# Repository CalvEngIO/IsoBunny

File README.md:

# IsoBunny
Optoisolator breakout module

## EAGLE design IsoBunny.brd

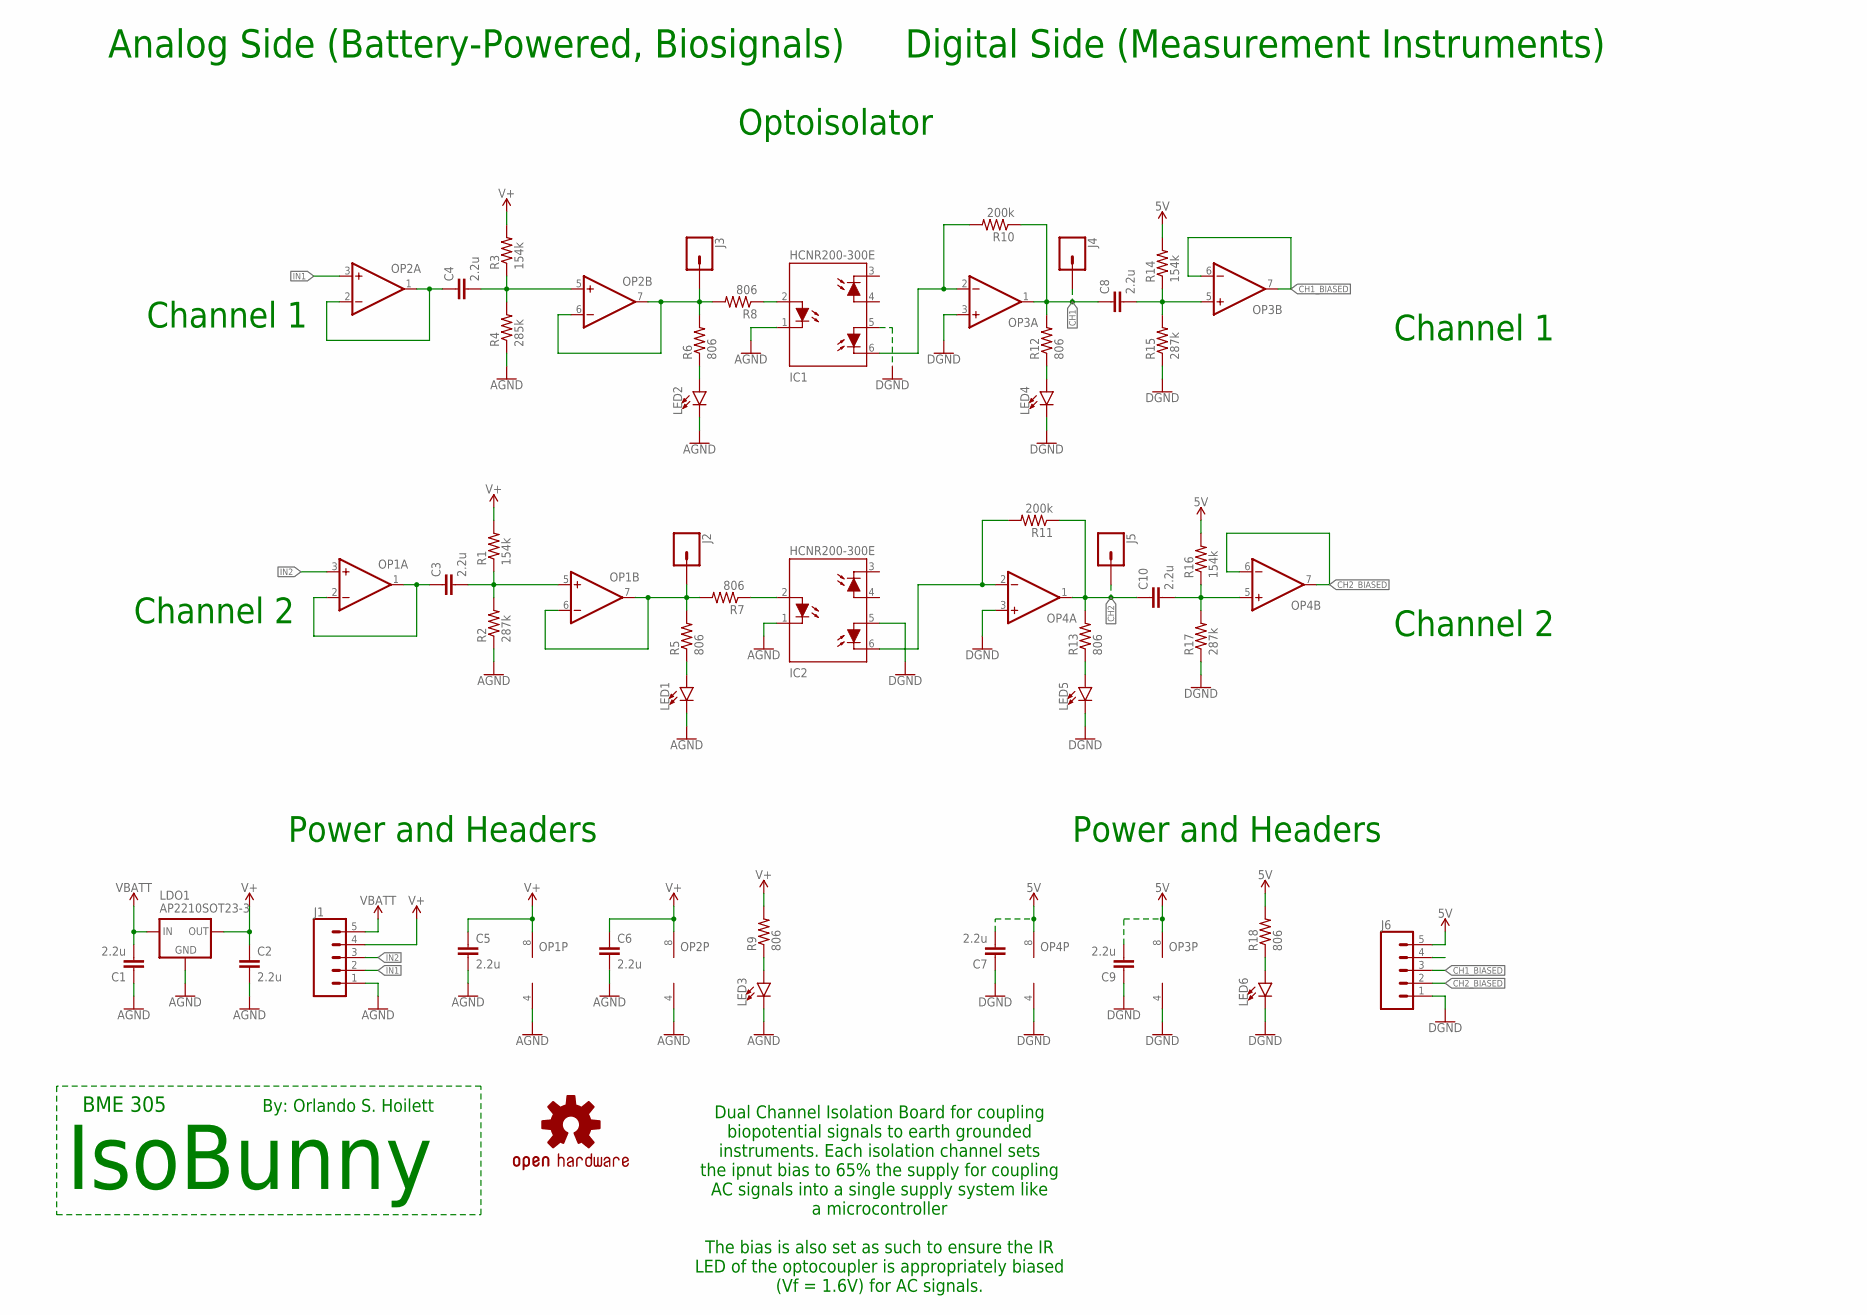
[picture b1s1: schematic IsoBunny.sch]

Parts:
C1, C2, C3, C4, C5, C6, C7, C8, C9, C10: 2.2u; C0603
IC1, IC2: HCNR200-300E; DIP8-400
J1, J6: CONN_05; 1X05
J2, J3, J4, J5: CONN_01PTH_NO_SILK_KIT; 1X01NS_KIT
LDO1: AP2210SOT23-3; SOT23
LED1, LED2, LED3, LED4, LED5, LED6: LED5MM; LED_5MM
LOGO1: OSHW-LOGOL; OSHW-LOGO-L
OP1, OP2, OP3, OP4: OP-DUALR; SO8
R1, R3, R14, R16: 154k; R0603
R2, R15, R17: 287k; R0603
R4: 285k; R0603
R5, R6, R7, R8, R9, R12, R13, R18: 806; R0603
R10, R11: 200k; R0603
REV1: REVISION.A; REV.A
U$1: PURDUE_BME_HANDLE; PURDUE_BME_HANDLE.1

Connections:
5V: C7.2, C9.2, J6.5, OP3.8 (V+), OP4.8 (V+), R14.2, R16.2, R18.2
AGND: C1.1, C2.2, C5.2, C6.2, IC1.1 (C), IC2.1 (C), J1.1, LDO1.1 (GND), LED1.K (C), LED2.K (C), LED3.K (C), OP1.4 (V-), OP2.4 (V-), R2.1, R4.1
CH1: C8.1, J4.1, OP3.1 (OUT), R10.1, R12.2
CH1_BIASED: J6.3, OP3.6 (-IN), OP3.7 (OUT)
CH2: C10.1, J5.1, OP4.1 (OUT), R11.1, R13.2
CH2_BIASED: J6.2, OP4.6 (-IN), OP4.7 (OUT)
DGND: C7.1, C9.1, IC1.5 (A2), IC2.5 (A2), J6.1, LED4.K (C), LED5.K (C), LED6.K (C), OP3.3 (+IN), OP3.4 (V-), OP4.3 (+IN), OP4.4 (V-), R15.1, R17.1
IN1: J1.2, OP2.3 (+IN)
IN2: J1.3, OP1.3 (+IN)
unnamed: C4.1, OP2.1 (OUT), OP2.2 (-IN)
unnamed: LED3.A, R9.1
unnamed: C4.2, OP2.5 (+IN), R3.1, R4.2
unnamed: C3.1, OP1.1 (OUT), OP1.2 (-IN)
unnamed: IC1.6 (C2), OP3.2 (-IN), R10.2
unnamed: C3.2, OP1.5 (+IN), R1.1, R2.2
unnamed: IC2.6 (C2), OP4.2 (-IN), R11.2
unnamed: LED6.A, R18.1
unnamed: IC2.2 (A), R7.1
unnamed: C10.2, OP4.5 (+IN), R16.1, R17.2
unnamed: LED2.A, R6.1
unnamed: IC1.2 (A), R8.1
unnamed: C8.2, OP3.5 (+IN), R14.1, R15.2
unnamed: LED4.A, R12.1
unnamed: LED1.A, R5.1
unnamed: LED5.A, R13.1
OUT1: J3.1, OP2.6 (-IN), OP2.7 (OUT), R6.2, R8.2
OUT2: J2.1, OP1.6 (-IN), OP1.7 (OUT), R5.2, R7.2
V+: C2.1, C5.1, C6.1, J1.4, LDO1.2 (OUT), OP1.8 (V+), OP2.8 (V+), R1.2, R3.2, R9.2
V_BATT: C1.2, J1.5, LDO1.3 (IN)

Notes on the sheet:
Analog Side (Battery-Powered, Biosignals)
Digital Side (Measurement Instruments)
Channel 1
Channel 2
Power and Headers
Optoisolator
Dual Channel Isolation Board for coupling biopotential signals to earth grounded instruments. Each isolation channel sets the ipnut bias to 65% the supply for coupling AC signals into a single supply system like a microcontroller The bias is also set as such to ensure the IR LED of the optocoupler 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
IsoBunny
BME 305
By: Orlando S. Hoilett

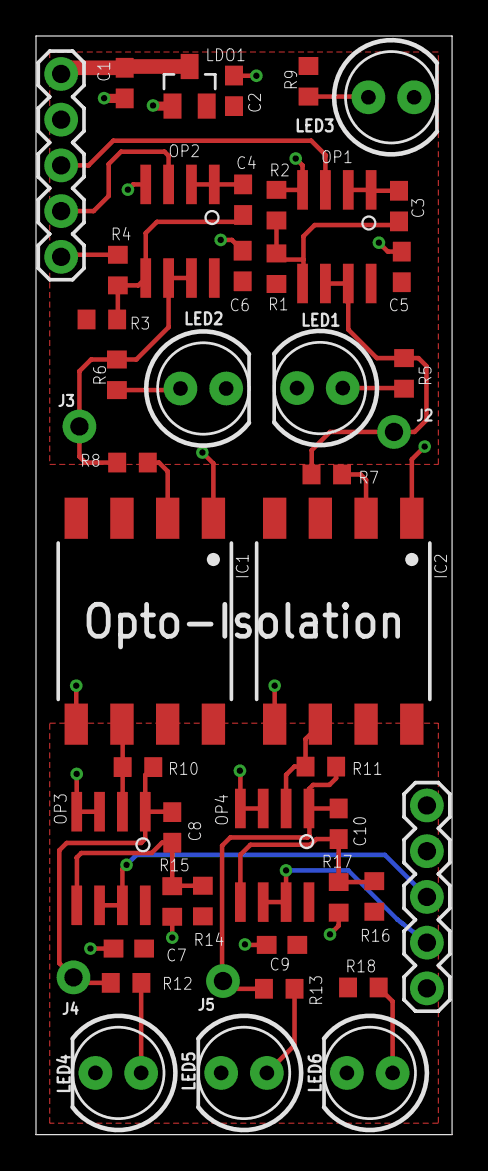
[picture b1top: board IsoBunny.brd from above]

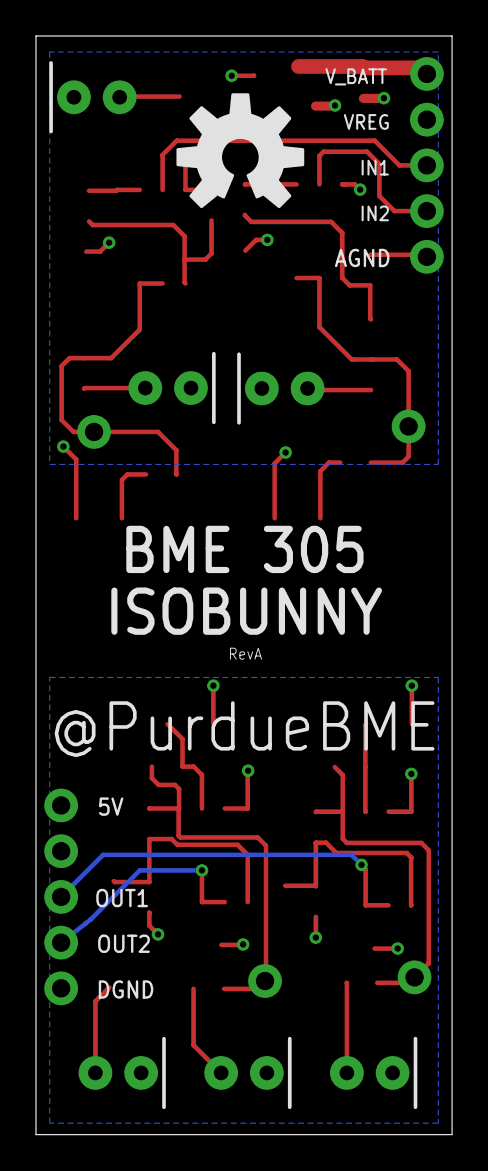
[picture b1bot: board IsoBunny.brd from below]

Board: 2 copper layers, 23.1 x 61.0 mm, 50 parts (3 on the bottom side), 29 nets.

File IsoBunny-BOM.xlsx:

IsoBunny Rev B |  |  |  |  |  |  |  |  |  |  | Total | 13.659999999999998 |  | 0.41860000000000003
BOM # | Comment | Designator | Description | Mounting Type | Package | Manufacturer | Manufacturer Part Number | Supplier | Supplier Part Number | Price per unit | Quantity | Price Total | 100 units | Price Total
1 | MCP6002 | OP1,OP4 | General Purpose Amplifier 2 Circuit Rail-to-Rail 8-SOIC | SMD | 8-SOIC | Microchip Technology | MCP6002T-I/SN | Digi-Key | MCP6002T-I/SNCT-ND | 0.34 | 2 | 0.68 |  | 0
2 | LM2904 | OP2,OP3 | General Purpose Amplifier 2 Circuit 8-SO | SMD | 8-SOIC | Diodes Incorporated | LM2904QS-13 | Digi-Key | LM2904QS-13DICT-ND | 0.38 | 2 | 0.76 | 0.20930000000000001 | 0.41860000000000003
3 | AP2210N-5.0 | LDO1 | Linear Voltage Regulator IC 1 Output 300mA SOT-23-5 | SMD | SOT-23-5 | Diodes Incorporated | AP2210N-5.0TRG1 | Digi-Key | AP2210N-5.0TRG1DICT-ND | 0.43 | 1 | 0.43 |  | 0
4 | HCNR200-300E | IC1,IC2 | Optoisolator Photovoltaic, Linearized Output 5000Vrms 1 Channel 8-DIP Gull Wing | SMD | 8-SMD, Gull Wing | Broadcom Limited | HCNR200-300E | Digi-Key | 516-1608-5-ND | 4.09 | 2 | 8.18 |  | 0
5 | Header Pins | J1,J2,J3,J4,J5,J6 | Connector Header Through Hole 40 position 0.100" (2.54mm)' | THT |  | Sullins Connector Solutions | PREC040SAAN-RC | Digi-Key | S1012EC-40-ND | 0.51 | 1 | 0.51 |  | 0
6 | 2.2uF capacitor | C1, C2,C3,C4,C5,C6,C7,C8,C9,C10 | 16V, X5R | SMD | 0603 | Murata Electronics North America | GRM188R61C225KE15D | Digi-Key | 490-3296-1-ND | 0.13 | 10 | 1.3 |  | 0
7 | 806 Ohm resistor | R5,R6,R7,R8,R9,R12,R13,R18 | 806 Ohms ±1% 0.1W, 1/10W Chip Resistor 0603 (1608 Metric) Automotive AEC-Q200 T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 | SMD | 0603 | Stackpole Electronics Inc. | RMCF0603FT806R | Digi-Key | RMCF0603FT806RCT-ND | 0.1 | 6 | 0.60000000000000009 |  | 0
8 | 154k resistor | R1,R3,R14,R16 | 154 kOhms ±1% 0.1W, 1/10W Chip Resistor 0603 (1608 Metric) Automotive AEC-Q200 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 | SMD | 0603 | Stackpole Electronics Inc. | RMCF0603FT154K | Digi-Key | RMCF0603FT154KCT-ND | 0.1 | 4 | 0.4 |  | 0
9 | 200k resistor | R10,R11 | 200 kOhms ±1% 0.1W, 1/10W Chip Resistor 0603 (1608 Metric) Moisture Resistant T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 | SMD | 0603 | Stackpole Electronics Inc. | CR0603-FX-2003ELF | Digi-Key | CR0603-FX-2003ELFCT-ND | 0.1 | 2 | 0.2 |  | 0
10 | 287k resistor | R2,R4,R15,R17 | 287 kOhms ±1% 0.1W, 1/10W Chip Resistor 0603 (1608 Metric) Automotive AEC-Q200 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 | SMD | 0603 | Stackpole Electronics Inc. | RMCF0603FT287K | Digi-Key | RMCF0603FT287KCT-ND | 0.1 | 4 | 0.4 |  | 0
11 | 402k resistor | R2,R4,R15,R17 | 402 kOhms ±1% 0.1W, 1/10W Chip Resistor 0603 (1608 Metric) Automotive AEC-Q200 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 | SMD | 0603 | Stackpole Electronics Inc. | RMCF0603FT402K | Digi-Key | RMCF0603FT402KCT-ND | 0.1 | 2 | 0.2 |  | 0

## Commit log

2019-06-02 committ with working designs
2019-06-02 renamed Gerber zip file
